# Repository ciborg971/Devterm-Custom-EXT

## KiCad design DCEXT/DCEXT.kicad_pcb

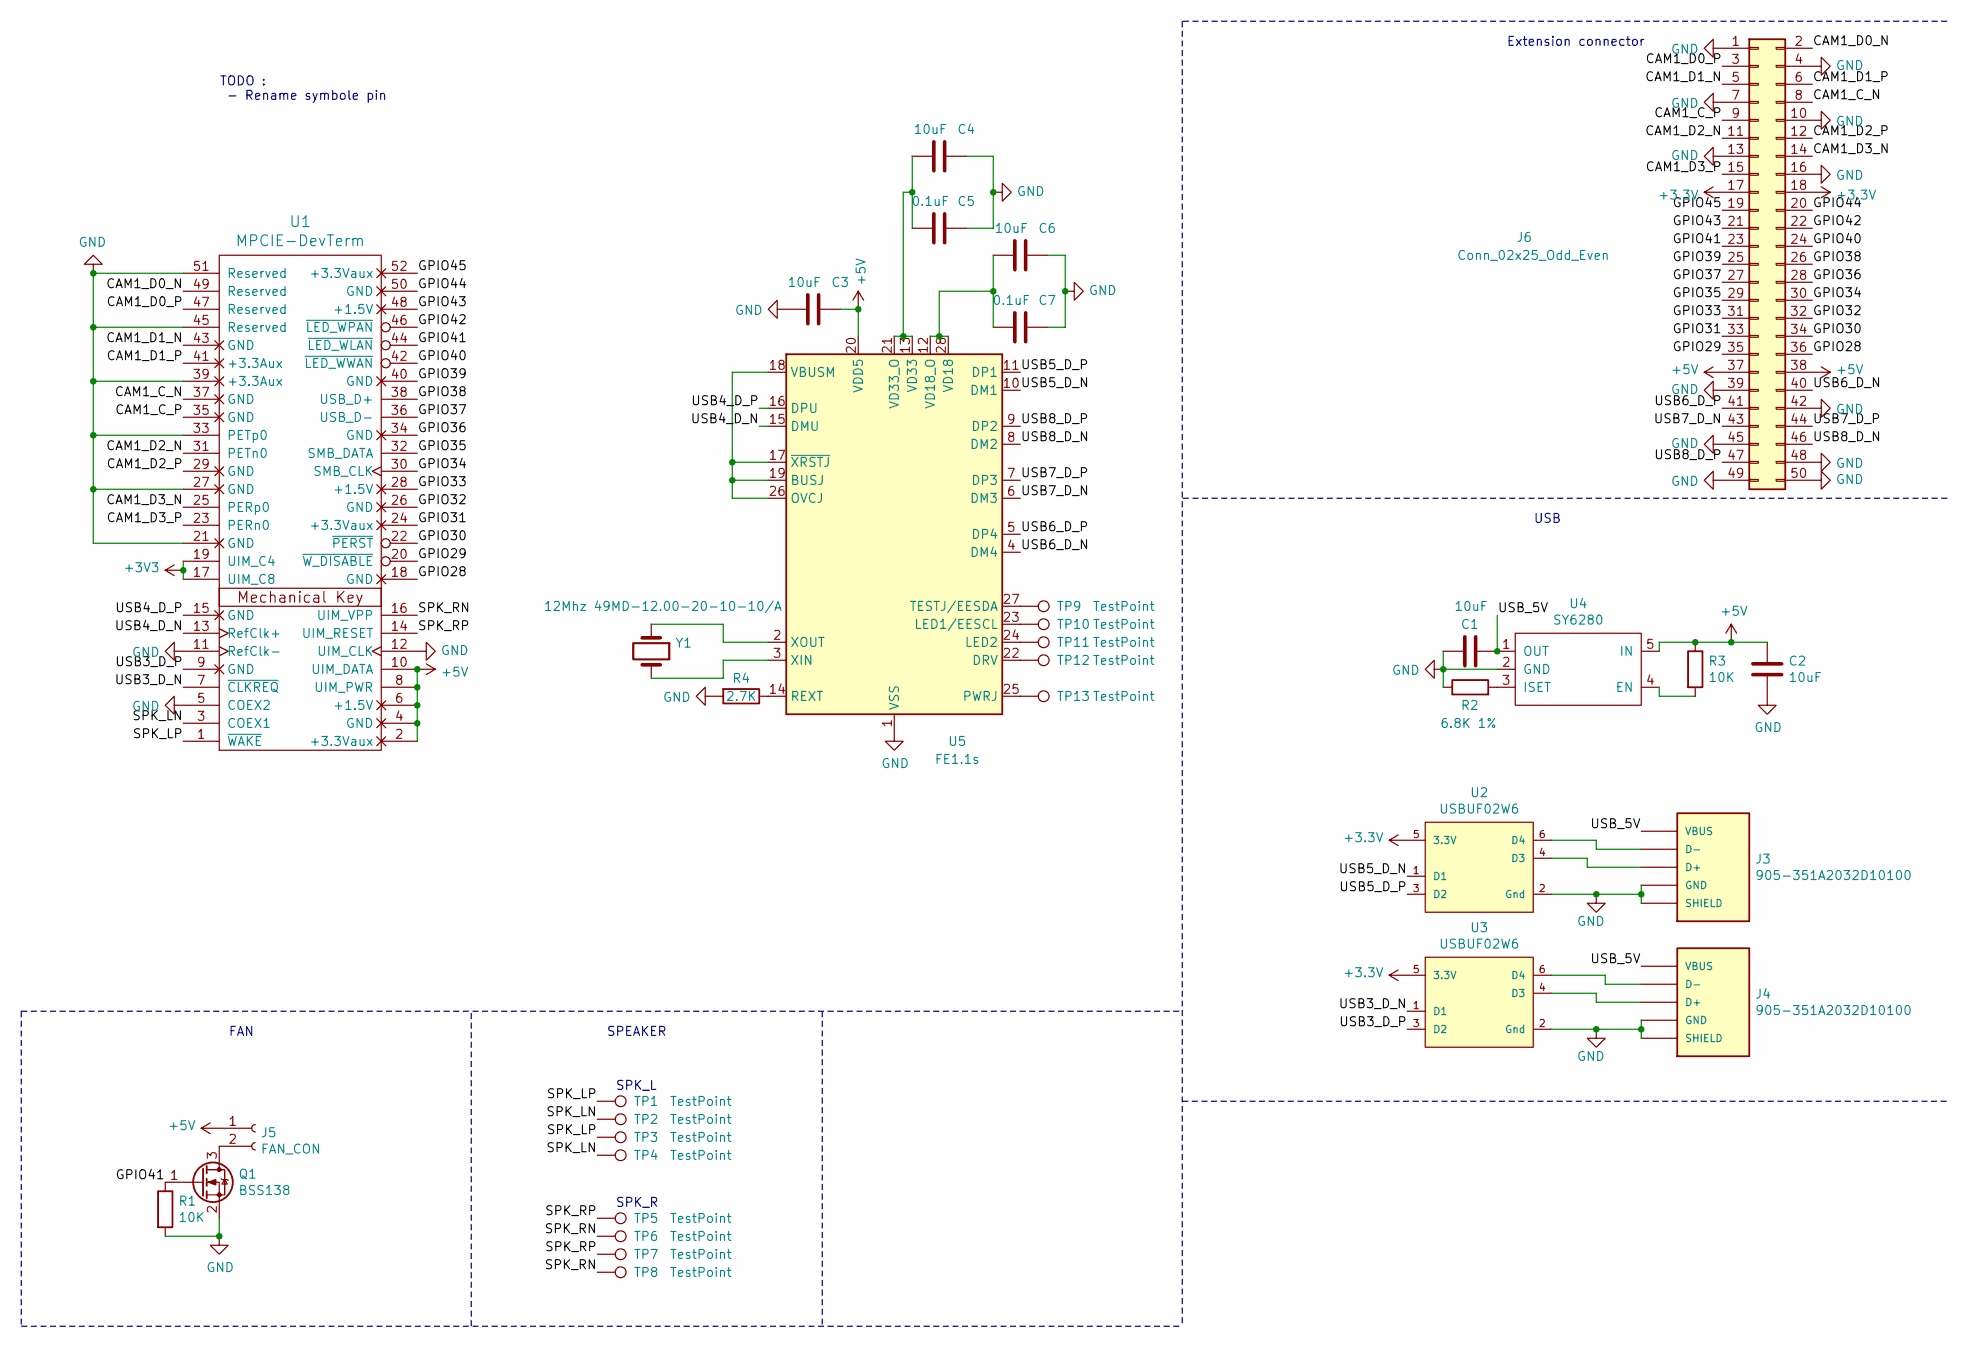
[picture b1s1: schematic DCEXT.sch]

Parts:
C1, C2, C3, C4, C6: 10uF; C_0402_1005Metric; LCSC C2846677
C5, C7: 0.1uF; C_0402_1005Metric; LCSC C41851
J3, J4: 905-351A2032D10100; USB-A-TH_USB-M-55-F; LCSC C42623
J5: FAN_CON; JST_PH_S2B-PH-K_1x02_P2.00mm_Horizontal; LCSC C160237
J6: Conn_02x25_Odd_Even; Hirose_FH12-50S-0.5SH_1x50-1MP_P0.50mm_Horizontal; LCSC C11098
Q1: BSS138; SOT-23; LCSC C427380
R1, R3: 10K; R_0402_1005Metric; LCSC C258091
R2: 6.8K 1%; R_0402_1005Metric; LCSC C208929
R4: 2.7K; R_0402_1005Metric; LCSC C168220
TP1, TP2, TP3, TP4, TP5, TP6, TP7, TP8: TestPoint; TestPoint_Pad_3.0x3.0mm
TP9, TP10, TP11, TP12, TP13: TestPoint; TestPoint_Pad_1.5x1.5mm
U1: MPCIE-DevTerm; devtermMPCIE
U2, U3: USBUF02W6; ST_Microelectronics-USBUF02W6-0; mouser part number 511-USBUF02W6; digikey description RC (Pi) EMI Filter 2nd Order Low Pass 2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
U4: SY6280; SOT-23-5_HandSoldering; LCSC C55136
U5: FE1.1s; SSOP-28_3.9x9.9mm_P0.635mm; LCSC C9359
Y1: 12Mhz 49MD-12.00-20-10-10/A; Crystal_SMD_HC49-SD; LCSC C240992

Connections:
+5V: C2.1, C3.1, J5.1, J6.37, J6.38, R3.1, U1.2 (+3.3Vaux), U1.4 (GND), U1.6 (+1.5V), U1.8 (UIM_PWR), U1.10 (UIM_DATA), U4.5 (IN), U5.20 (VDD5)
/CAM1_C_N: J6.8, U1.37 (GND)
/CAM1_C_P: J6.9, U1.35 (GND)
/CAM1_D0_N: J6.2, U1.49 (Reserved)
/CAM1_D0_P: J6.3, U1.47 (Reserved)
/CAM1_D1_N: J6.5, U1.43 (GND)
/CAM1_D1_P: J6.6, U1.41 (+3.3Aux)
/CAM1_D2_N: J6.11, U1.31 (PETn0)
/CAM1_D2_P: J6.12, U1.29 (GND)
/CAM1_D3_N: J6.14, U1.25 (PERp0)
/CAM1_D3_P: J6.15, U1.23 (PERn0)
/GPIO28: J6.36, U1.18 (GND)
/GPIO29: J6.35, U1.20 (~W_DISABLE)
/GPIO30: J6.34, U1.22 (~PERST)
/GPIO31: J6.33, U1.24 (+3.3Vaux)
/GPIO32: J6.32, U1.26 (GND)
/GPIO33: J6.31, U1.28 (+1.5V)
/GPIO34: J6.30, U1.30 (SMB_CLK)
/GPIO35: J6.29, U1.32 (SMB_DATA)
/GPIO36: J6.28, U1.34 (GND)
/GPIO37: J6.27, U1.36 (USB_D-)
/GPIO38: J6.26, U1.38 (USB_D+)
/GPIO39: J6.25, U1.40 (GND)
/GPIO40: J6.24, U1.42 (~LED_WWAN)
/GPIO41: J6.23, Q1.1 (G), R1.1, U1.44 (~LED_WLAN)
/GPIO42: J6.22, U1.46 (~LED_WPAN)
/GPIO43: J6.21, U1.48 (+1.5V)
/GPIO44: J6.20, U1.50 (GND)
/GPIO45: J6.19, U1.52 (+3.3Vaux)
/SPK_LN: TP2.1, TP4.1, U1.3 (COEX1)
/SPK_LP: TP1.1, TP3.1, U1.1 (~WAKE)
/SPK_RN: TP6.1, TP8.1, U1.16 (UIM_VPP)
/SPK_RP: TP5.1, TP7.1, U1.14 (UIM_RESET)
/USB3_D_N: U1.7 (~CLKREQ), U3.1 (D1)
/USB3_D_P: U1.9 (GND), U3.3 (D2)
/USB4_D_N: U1.13 (RefClk+), U5.15 (DMU)
/USB4_D_P: U1.15 (GND), U5.16 (DPU)
/USB5_D_N: U2.1 (D1), U5.10 (DM1)
/USB5_D_P: U2.3 (D2), U5.11 (DP1)
/USB6_D_N: J6.40, U5.4 (DM4)
/USB6_D_P: J6.41, U5.5 (DP4)
/USB7_D_N: J6.43, U5.6 (DM3)
/USB7_D_P: J6.44, U5.7 (DP3)
/USB8_D_N: J6.46, U5.8 (DM2)
/USB8_D_P: J6.47, U5.9 (DP2)
/USB_5V: C1.2, J3.1 (VBUS), J4.1 (VBUS), U4.1 (OUT)
GND: C1.1, C2.2, C3.2, C4.1, C5.1, C6.1, C7.1, J3.4 (GND), J3.5 (SHIELD), J3.6 (SHIELD), J3.7 (SHIELD), J3.8 (SHIELD), J4.4 (GND), J4.5 (SHIELD), J4.6 (SHIELD), J4.7 (SHIELD), J4.8 (SHIELD), J6.1, J6.4, J6.7, J6.10, J6.13, J6.16, J6.39, J6.42, J6.45, J6.48, J6.49, J6.50, Q1.2 (S), R1.2, R2.1, R4.2, U1.5 (COEX2), U1.11 (RefClk-), U1.12 (UIM_CLK), U1.21 (GND), U1.27 (GND), U1.33 (PETp0), U1.39 (+3.3Aux), U1.45 (Reserved), U1.51 (Reserved), U2.2 (Gnd), U3.2 (Gnd), U4.2 (GND), U5.1 (VSS)
unnamed: C4.2, C5.2, U5.13 (VD33), U5.21 (VD33_O)
unnamed: C6.2, C7.2, U5.12 (VD18_O), U5.28 (VD18)
unnamed: J3.2 (D-), U2.6 (D4)
unnamed: J3.3 (D+), U2.4 (D3)
unnamed: J4.2 (D-), U3.6 (D4)
unnamed: J4.3 (D+), U3.4 (D3)
unnamed: J5.2, Q1.3 (D)
unnamed: R2.2, U4.3 (ISET)
unnamed: R3.2, U4.4 (EN)
unnamed: R4.1, U5.14 (REXT)
unnamed: TP9.1, U5.27 (TESTJ/EESDA)
unnamed: TP10.1, U5.23 (LED1/EESCL)
unnamed: TP11.1, U5.24 (LED2)
unnamed: TP12.1, U5.22 (DRV)
unnamed: TP13.1, U5.25 (PWRJ)
unnamed: U5.2 (XOUT), Y1.1
unnamed: U5.3 (XIN), Y1.2
unnamed: U5.17 (~XRSTJ), U5.18 (VBUSM), U5.19 (BUSJ), U5.26 (OVCJ)

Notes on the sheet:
FAN
SPEAKER
USB
TODO : - Rename symbole pin
Extension connector
SPK_L
SPK_R

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
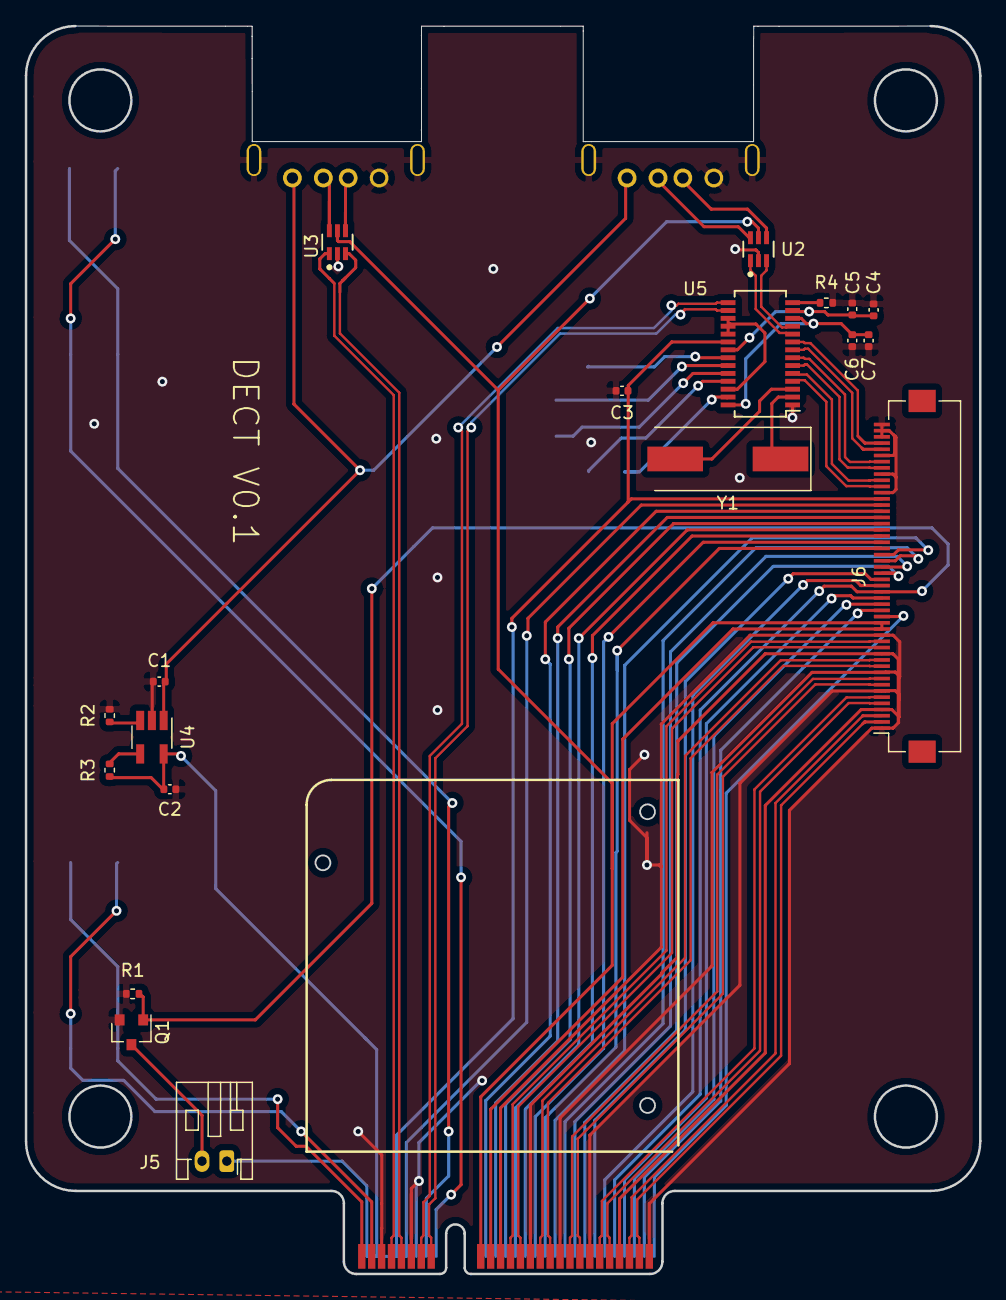
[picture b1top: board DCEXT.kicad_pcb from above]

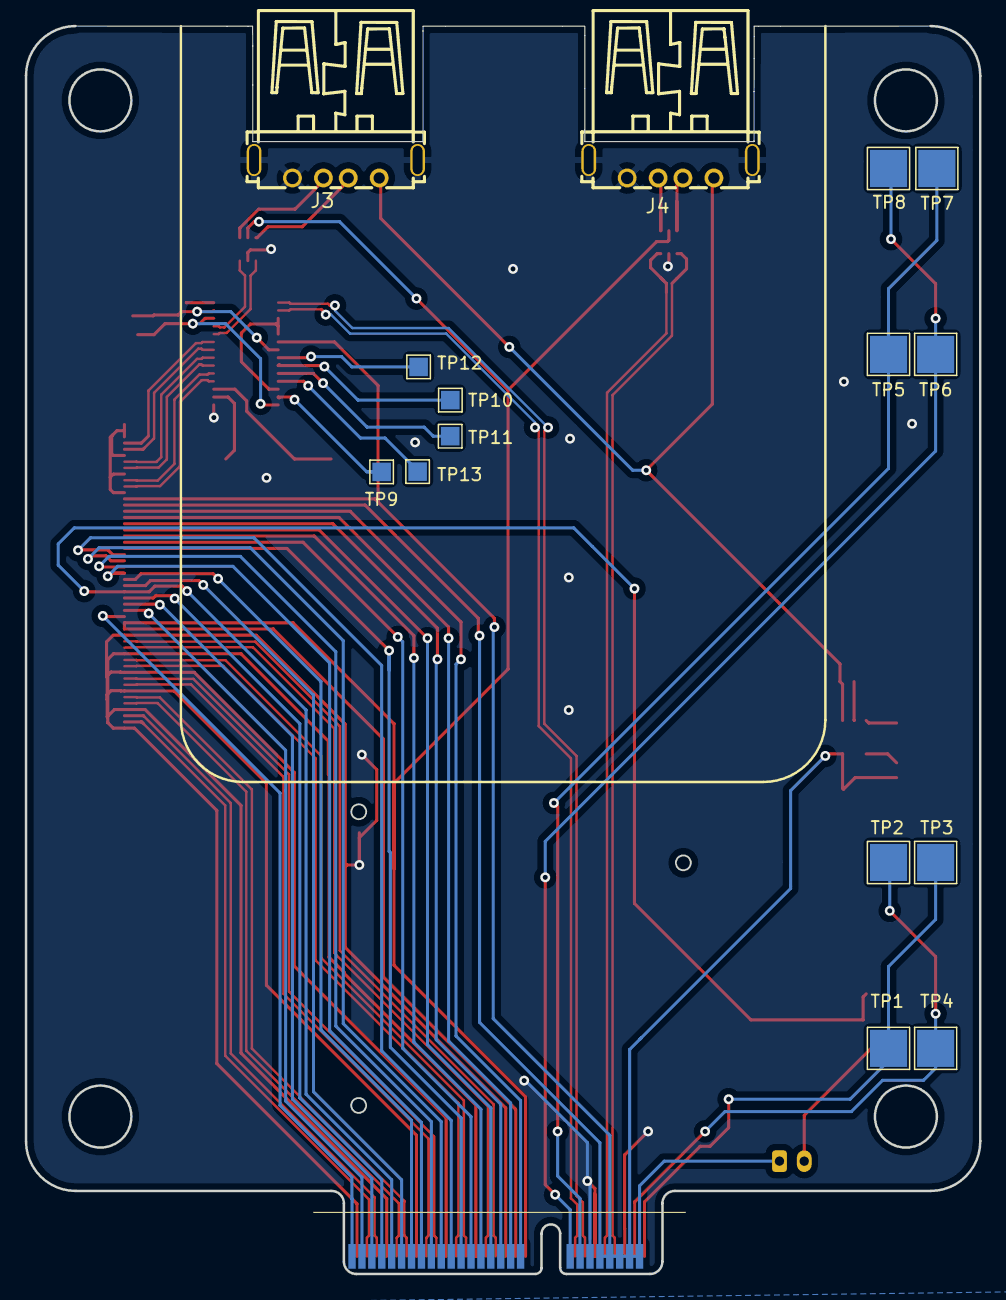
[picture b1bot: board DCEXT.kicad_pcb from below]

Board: 2 copper layers, 77.0 x 100.7 mm, 35 parts (15 on the bottom side), 66 nets.

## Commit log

2021-09-12 Add original EXT module documentation
2021-09-12 Add pcb outline, mpcie connector and holes (hole position is not accurate)
2021-09-12 Add usb host connector and add more documentation
2021-09-12 Add usb protection, fan control and fpc connector for module
2021-09-14 Update schematic of original EXT module (compoment value), add reference dxf file
2021-09-14 Add updated dxf from clockwork and converted it for kicad
    Tutorial to convert a dxf to kicad format ; https://github.com/KiCad/kicad-doc/blob/master/src/pcbnew/pcbnew_create_and_modify_board.adoc
2021-09-14 Fix usb position,holes and pcb outline, add current limiter
2021-09-15 Progess
    Pop OS and kicad decided i didnt need 3d acceleration anymore, switching to mac
2021-11-13 Fix usb position (for the last time !), speaker connector and routing
2021-11-13 Add USB hub, routing and start part sourcing
    Spoiller alert : everything is out of stock ...
2021-12-01 Change USB connector to something in stock :/ + gerber files
